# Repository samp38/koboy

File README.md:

# Kobo Mini to Flight Computer Kit

## Description
Turn your kobo mini into a complete flight instrument :-)
This project allows you to build an extension card for Kobo which runs XCSoar. The extension card includes a GPS and a pressure sensor. It acts as a sound variometer while it sends data (GPS NMEA data, Vz, temperature, absolute pressure) to XCSoar. In this repo you will find:
- Eagle files and guide to realize the electronic card
- Firmware source (and precompiled hex binaries) for the mcu
- STL parts for the Kobo Mini to receive electronic card (and a bigger battery for long flights)
- XCSoar software for Kobo

### How it works
The GPS chip is standalone. As long as it's powered, it runs and sends NMEA data through its TX output at a given (user definable) frequency. The microntroller manages the pressure sensing and computing: pressure is measured, numerically filtered and derivated at 50Hz to provide Vz. To work with the GPS chip, the microcontroller detects the beginning of the PA6H TX communication and waits the time needed to send variometer data between GPS data bursts. It can seem dubious but it works very well for years in my case. The variometer data sent by the microcontroller to XCSoar mimics a Digifly Leonardo. So you just have to select Digifly Leonardo in XCSoar to have the variometer data read and understood by XCSoar. All the steps of the XCSoar configuration is described in the __software__ part.

### Two versions for two interaction options
To control the sound vario volume and turn the extension card on/off (indeed, you might want to use your Kobo as a reader), there are two possibilities and thus two versions of the PCB:
- "button version": meaningful. Short press to loop in sound levels and long press to turn off.
- "tap-tap version": the button is replaced with a accelerometer which detects the tap. Single tap to loop in sound levels and double tap to turn on/off.

## Hardware

The extension card is based on a [PIC24F16KA101](http://ww1.microchip.com/downloads/en/DeviceDoc/39927c.pdf) microcontroller, a GPS patch antenna chip [(PA6H)](https://cdn-shop.adafruit.com/datasheets/GlobalTop-FGPMMOPA6H-Datasheet-V0A.pdf) and a high resolution pressure sensor [(MS5611)](https://infusionsystems.com/support/MS5611-01BA03.pdf).

The GPS (U5) symbol and footprint come from [Gekkio's KiCad libraries](https://github.com/Gekkio/gekkio-kicad-libs) by Joonas Javanainen, licensed under CC BY 4.0 (copy in `hardware/PCB/Vario Kobo/Button_version/kicad-koboy_button_side/libs/gekkio/`).

## Firmware

Compiled with Microchip XC16 compiler

## Software

XCSoar

## Open issues

### Schematic
- No VDD pin on the programming connector: the PIC must be powered separately while flashing.
- MCLR: the series resistor R2 (100Ω to 470Ω) from the datasheet's reference circuit is missing (C6 100nF sits directly on the MCLR net). It limits the current dumped by the capacitor if the pin breaks down under ESD/EOS (PIC24F16KA102 datasheet, §2.3).
- No local decoupling capacitor on the MAS6240 VIN.
- KOBO_RX is shared between the PIC and the GPS TX (through R5).
- Button version: the MAS6240 EN1/EN2 pins are wired to RA2/RA3, the reverse of `firmware/audio.c` (`EN1 = _RA3`, `EN2 = _RA2`). This dates back to the original Eagle design. As a result the low and medium volume levels are swapped (low gives 2x, medium gives 1x); high and off are unaffected. The taptap version matches the firmware. To be fixed in the firmware with per-version pin definitions.
- R7 (1Ω) in series with the piezo is nearly a jumper: the MAS6240 datasheet suggests an optional 1kΩ to 2kΩ output protection resistor.
- Taptap version: the PIC is programmed through the USB-A plug X1 with a custom pinout (D+ → MCLR, D− → PGC, 5V → PGD, which is also the GPS RX). Plugging the board into a real USB port would put 5V on PGD and the GPS RX.
- Taptap version: the PA6H GND pins 3, 12 and 19 are not connected (Eagle library), only pin 8 is. To be fixed with the Gekkio GPS footprint, as on the button version.

### PCB
- Button version, DRC: 2 silkscreen warnings, no errors: the BZ1 (buzzer) footprint outline from the Eagle import runs over its pads. The fab clips it.
- Taptap version, DRC: 12 errors, all pad-to-pad gaps of 0.195mm (rule 0.2mm) inside the Eagle MMA8452 footprint (0.305mm pads at 0.5mm pitch); to be fixed with a KiCad standard footprint. Silkscreen warnings from the Eagle PA6H and MMA8452 outlines and undersized texts.

### Firmware
- Auto-shutdown after inactivity is not implemented: `vario_shutdown_tick()` counts down but the `shutdown()` call is commented out (`firmware/vario.c`).

### Repository / documentation
- The hardware moved from Eagle to KiCad, with the same structure for both versions (`main` sheet plus a `Power supply` sub-sheet):
  - button version: `hardware/PCB/Vario Kobo/Button_version/kicad-koboy_button_side/main.kicad_pro`;
  - taptap version: `hardware/PCB/Vario Kobo/Taptap_version/kicad-koboy_taptap_side/main.kicad_pro` (migration in progress: references, silkscreen, GPS footprint and pin types still to do).

  The Eagle files are kept for history only; "Vario Kobo TOP" is to be removed.
- The README still says "Eagle files" in the description and needs updating for KiCad.

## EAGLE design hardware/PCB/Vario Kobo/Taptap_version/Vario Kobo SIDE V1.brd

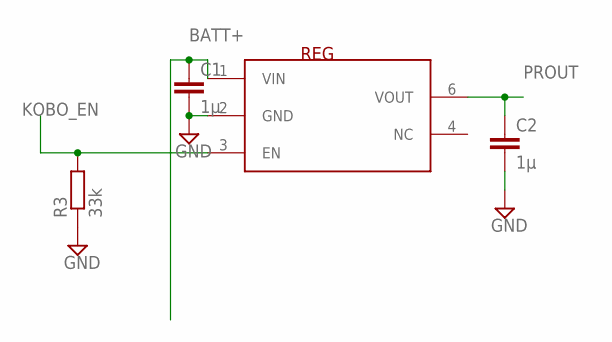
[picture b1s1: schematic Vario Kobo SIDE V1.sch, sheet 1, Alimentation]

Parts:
C1, C2: 1µ; C0603
R3: 33k; R0603
REG: ADP160/161/162/163; TSOT23-6_DDC

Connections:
BATT+: C1.1, REG.1 (VIN); also elsewhere on the board
GND: C1.2, C2.2, R3.1, REG.2 (GND); also elsewhere on the board
KOBO_EN: R3.2, REG.3 (EN); also elsewhere on the board
PROUT: C2.1, REG.6 (VOUT); also elsewhere on the board

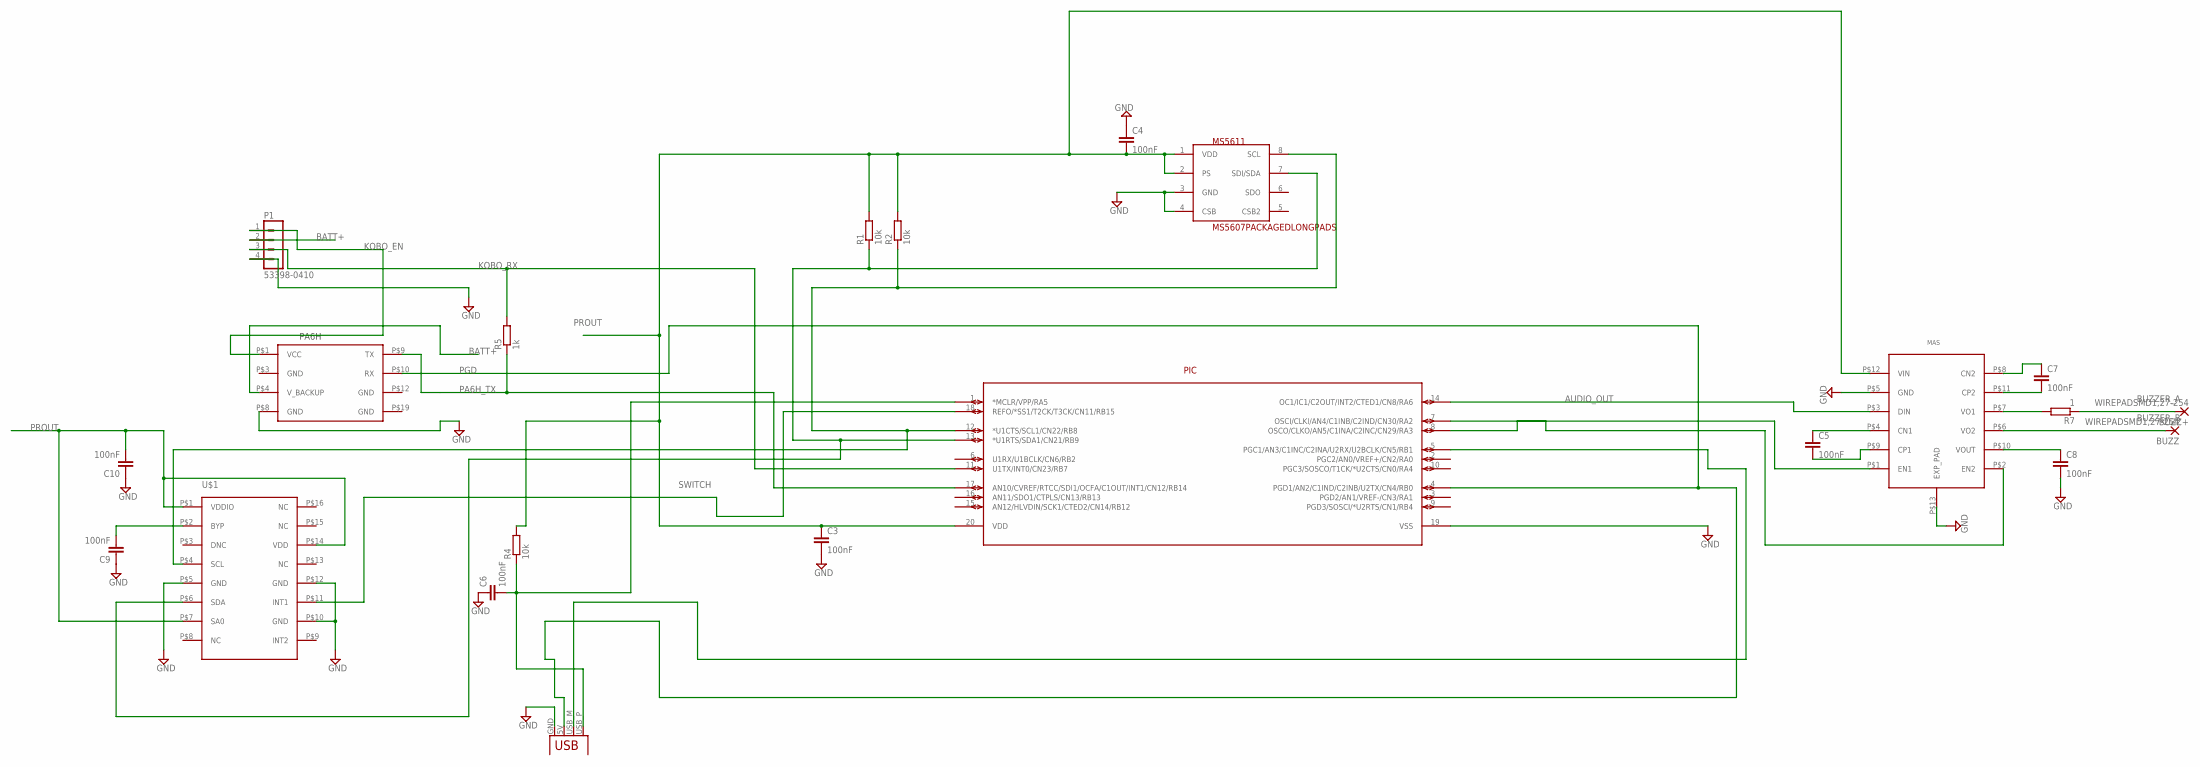
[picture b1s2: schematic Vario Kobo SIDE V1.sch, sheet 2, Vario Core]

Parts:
BUZZ: WIREPADSMD1,27-254; SMD1,27-2,54
BUZZ+: WIREPADSMD1,27-254; SMD1,27-2,54
C3, C4, C5, C6, C7, C8, C9, C10: 100nF; C0603
MAS: MAS6240; QFN12_3X3_LONGPADS
MS5611: MS5607PACKAGEDLONGPADS; MS5607-02BA03_LONGPADS
P1: 53398-0410
PA6H: PA6H; PA6H_PRINT
PIC: PIC24F16KA101-X_; SSOP20_MC
R1, R2, R4: 10k; R0603
R5: 1k; R0603
R7: 1; R0603
U$1: MMA8452LONGPADS; MMA845X_LONG_PADS
X1: USBPCB; USB-A-PCB

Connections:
AUDIO_OUT: MAS.P$3 (DIN), PIC.14 (OC1/IC1/C2OUT/INT2/CTED1/CN8/RA6)
BATT+: P1.2, PA6H.P$4 (V_BACKUP); also elsewhere on the board
BUZZER_A: BUZZ+.1, R7.1
BUZZER_B: BUZZ.1, MAS.P$6 (VO2)
GND: C3.2, C4.1, C6.1, C8.2, C9.1, C10.1, MAS.P$5 (GND), MAS.P$13 (EXP_PAD), MS5611.3 (GND), MS5611.4 (CSB), P1.4, PA6H.P$8 (GND), PIC.19 (VSS), U$1.P$5 (GND), U$1.P$10 (GND), U$1.P$12 (GND), X1.GND; also elsewhere on the board
KOBO_EN: P1.1, PA6H.P$1 (VCC); also elsewhere on the board
KOBO_RX: P1.3, PIC.11 (U1TX/INT0/CN23/RB7), R5.2
MCLR: C6.2, PIC.1 (*MCLR/VPP/RA5), R4.1, X1.USB_P (D+)
unnamed: C8.1, MAS.P$10 (VOUT)
unnamed: C5.1, MAS.P$4 (CN1)
unnamed: C5.2, MAS.P$9 (CP1)
unnamed: C7.2, MAS.P$11 (CP2)
unnamed: C7.1, MAS.P$8 (CN2)
unnamed: MAS.P$7 (VO1), R7.2
unnamed: MAS.P$1 (EN1), PIC.8 (OSCO/CLKO/AN5/C1INA/C2INC/CN29/RA3)
unnamed: C9.2, U$1.P$2 (BYP)
unnamed: MAS.P$2 (EN2), PIC.7 (OSCI/CLKI/AN4/C1INB/C2IND/CN30/RA2)
PA6H_TX: PA6H.P$9 (TX), PIC.17 (AN10/CVREF/RTCC/SDI1/OCFA/C1OUT/INT1/CN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), R5.1
PGC: PIC.5 (PGC1/AN3/C1INC/C2INA/U2RX/U2BCLK/CN5/RB1), X1.USB_M (D-)
PGD: PA6H.P$10 (RX), PIC.4 (PGD1/AN2/C1IND/C2INB/U2TX/CN4/RB0), X1.5V (VBUS)
PROUT: C3.1, C4.2, C10.2, MAS.P$12 (VIN), MS5611.1 (VDD), MS5611.2 (PS), PIC.20 (VDD), R1.2, R2.2, R4.2, U$1.P$1 (VDDIO), U$1.P$7 (SA0), U$1.P$14 (VDD); also elsewhere on the board
SCL: MS5611.8 (SCL), PIC.12 (*U1CTS/SCL1/CN22/RB8), R2.1, U$1.P$4 (SCL)
SDA: MS5611.7 (SDI/SDA), PIC.13 (*U1RTS/SDA1/CN21/RB9), R1.1, U$1.P$6 (SDA)
SWITCH: PIC.18 (REFO/*SS1/T2CK/T3CK/CN11/RB15), U$1.P$11 (INT1)

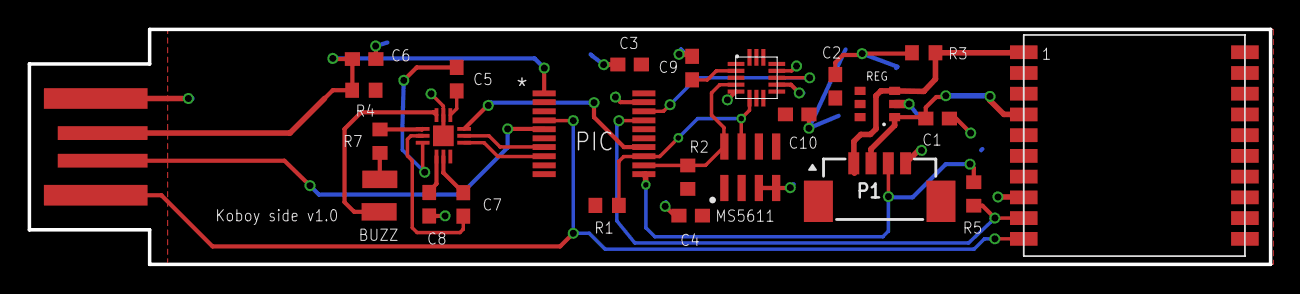
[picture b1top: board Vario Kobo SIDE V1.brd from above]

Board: 2 copper layers, 89.8 x 17.0 mm, 26 parts (0 on the bottom side), 24 nets.

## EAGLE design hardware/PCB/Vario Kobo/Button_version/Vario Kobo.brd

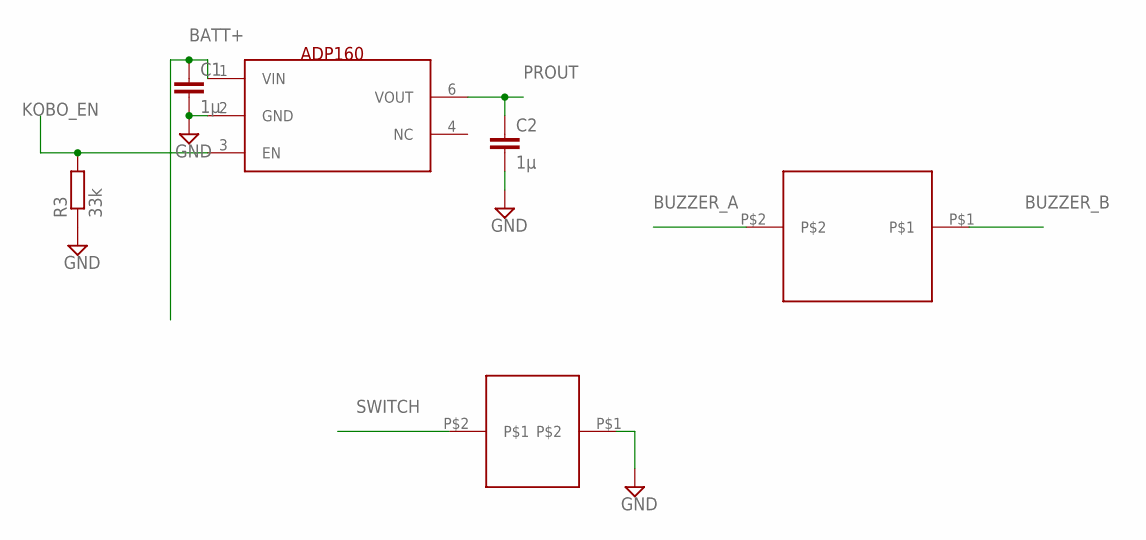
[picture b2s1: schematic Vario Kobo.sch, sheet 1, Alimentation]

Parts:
ADP160: ADP160/161/162/163; TSOT23-6_DDC
BUTTON: SMS_J_LEAD
BUZZER: PKLCS1212E2000-R1; PKLCS1212E2000-R1-SMD
C1, C2: 1µ; C0603
R3: 33k; R0603

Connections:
BATT+: ADP160.1 (VIN), C1.1; also elsewhere on the board
BUZZER_A: BUZZER.P$2; also elsewhere on the board
BUZZER_B: BUZZER.P$1; also elsewhere on the board
GND: ADP160.2 (GND), BUTTON.P$1, C1.2, C2.2, R3.1; also elsewhere on the board
KOBO_EN: ADP160.3 (EN), R3.2; also elsewhere on the board
PROUT: ADP160.6 (VOUT), C2.1; also elsewhere on the board
SWITCH: BUTTON.P$2; also elsewhere on the board

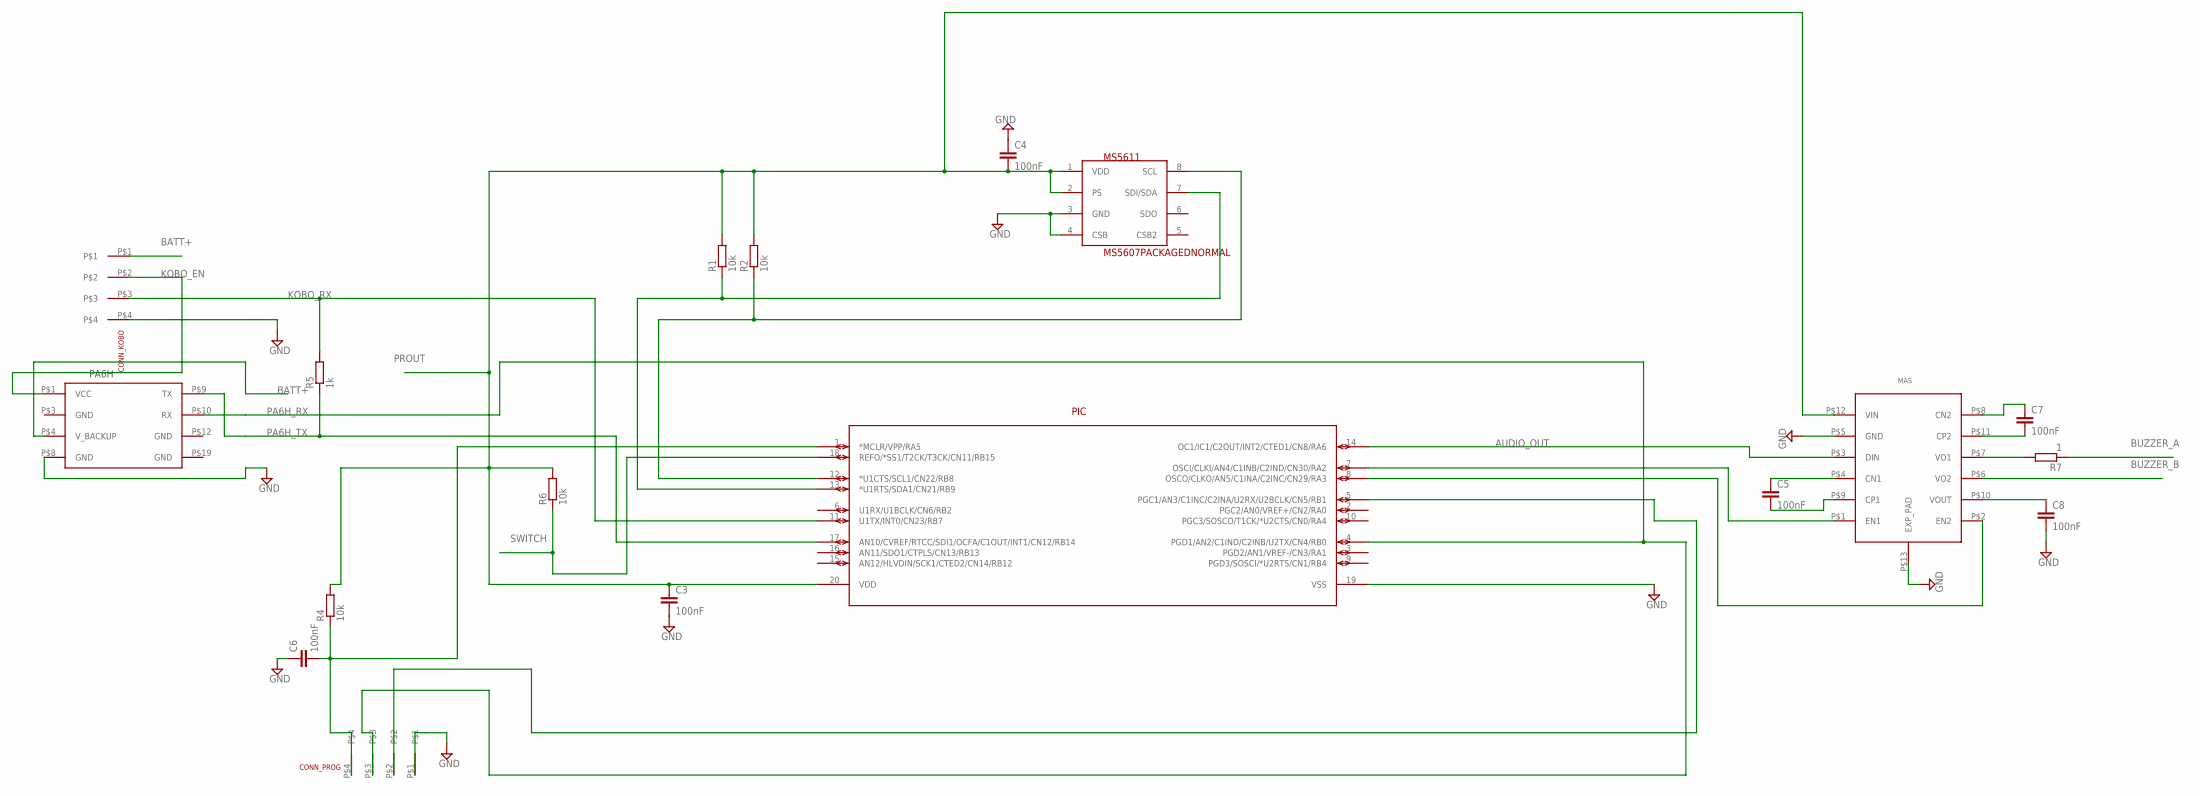
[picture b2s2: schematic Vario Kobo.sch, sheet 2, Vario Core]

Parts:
C3, C4, C5, C6, C7, C8: 100nF; C0603
CONN_KOBO: PICO-EZMATE4; PICO-EZMATE4-PCB
CONN_PROG: PICO-EZMATE4; PICO-EZMATE4-PCB
MAS: MAS6240; QFN12_3X3_LONGPADS
MS5611: MS5607PACKAGEDNORMAL; MS5607-02BA03
PA6H: PA6H; PA6H_PRINT
PIC: PIC24F16KA101-X_; SSOP20_MC
R1, R2, R4, R6: 10k; R0603
R5: 1k; R0603
R7: 1; R0603

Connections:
AUDIO_OUT: MAS.P$3 (DIN), PIC.14 (OC1/IC1/C2OUT/INT2/CTED1/CN8/RA6)
BATT+: CONN_KOBO.P$1, PA6H.P$4 (V_BACKUP); also elsewhere on the board
BUZZER_A: R7.1; also elsewhere on the board
BUZZER_B: MAS.P$6 (VO2); also elsewhere on the board
GND: C3.2, C4.1, C6.1, C8.2, CONN_KOBO.P$4, CONN_PROG.P$1, MAS.P$5 (GND), MAS.P$13 (EXP_PAD), MS5611.3 (GND), MS5611.4 (CSB), PA6H.P$8 (GND), PIC.19 (VSS); also elsewhere on the board
KOBO_EN: CONN_KOBO.P$2, PA6H.P$1 (VCC); also elsewhere on the board
KOBO_RX: CONN_KOBO.P$3, PIC.11 (U1TX/INT0/CN23/RB7), R5.2
MCLR: C6.2, CONN_PROG.P$4, PIC.1 (*MCLR/VPP/RA5), R4.1
unnamed: C8.1, MAS.P$10 (VOUT)
unnamed: C5.1, MAS.P$4 (CN1)
unnamed: C5.2, MAS.P$9 (CP1)
unnamed: C7.2, MAS.P$11 (CP2)
unnamed: C7.1, MAS.P$8 (CN2)
unnamed: MAS.P$7 (VO1), R7.2
unnamed: MAS.P$1 (EN1), PIC.7 (OSCI/CLKI/AN4/C1INB/C2IND/CN30/RA2)
unnamed: MAS.P$2 (EN2), PIC.8 (OSCO/CLKO/AN5/C1INA/C2INC/CN29/RA3)
PA6H_RX: CONN_PROG.P$3, PA6H.P$10 (RX), PIC.4 (PGD1/AN2/C1IND/C2INB/U2TX/CN4/RB0)
PA6H_TX: PA6H.P$9 (TX), PIC.17 (AN10/CVREF/RTCC/SDI1/OCFA/C1OUT/INT1/CN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), R5.1
PGC: CONN_PROG.P$2, PIC.5 (PGC1/AN3/C1INC/C2INA/U2RX/U2BCLK/CN5/RB1)
PROUT: C3.1, C4.2, MAS.P$12 (VIN), MS5611.1 (VDD), MS5611.2 (PS), PIC.20 (VDD), R1.2, R2.2, R4.2, R6.2; also elsewhere on the board
SCL: MS5611.8 (SCL), PIC.12 (*U1CTS/SCL1/CN22/RB8), R2.1
SDA: MS5611.7 (SDI/SDA), PIC.13 (*U1RTS/SDA1/CN21/RB9), R1.1
SWITCH: PIC.18 (REFO/*SS1/T2CK/T3CK/CN11/RB15), R6.1; also elsewhere on the board

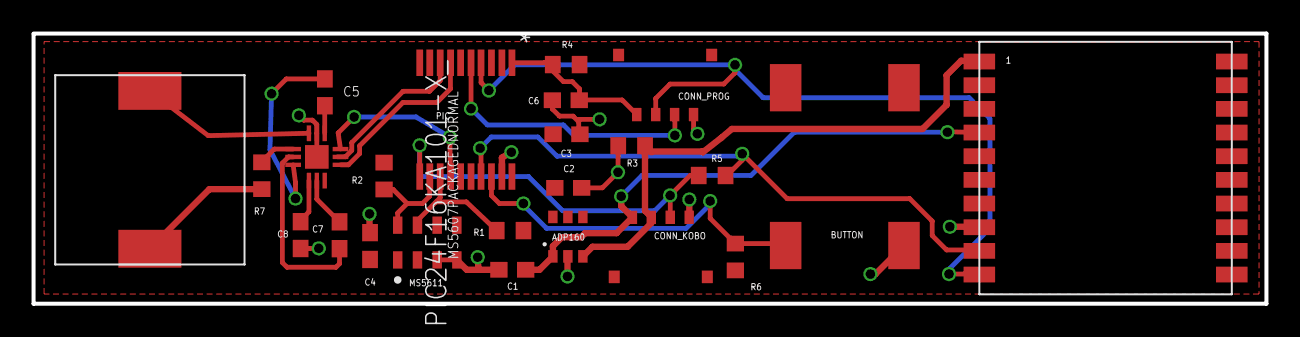
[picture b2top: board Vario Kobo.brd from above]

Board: 2 copper layers, 78.1 x 17.1 mm, 24 parts (0 on the bottom side), 23 nets.

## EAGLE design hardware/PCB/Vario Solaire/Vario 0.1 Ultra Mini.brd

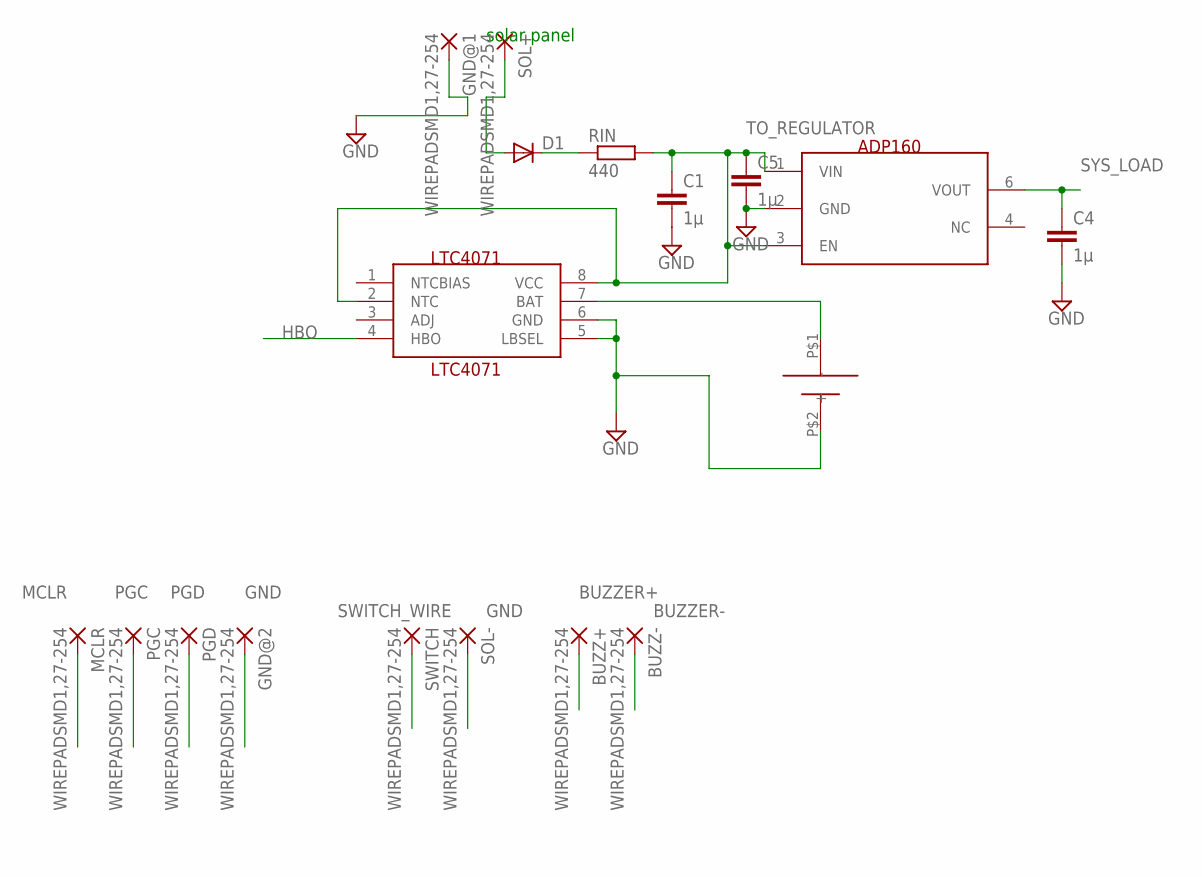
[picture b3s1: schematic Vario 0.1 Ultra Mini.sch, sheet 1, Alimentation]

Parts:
ADP160: ADP160/161/162/163; TSOT23-6_DDC
BATT+: VARIO_LIPO
BUZZ+: WIREPADSMD1,27-254; SMD1,27-2,54
BUZZ-: WIREPADSMD1,27-254; SMD1,27-2,54
C1, C4, C5: 1µ; C0603
D1: DIODE-SOD323-R; SOD323-R
GND@1, GND@2: WIREPADSMD1,27-254; SMD1,27-2,54
LTC4071: LTC4071; MSOP8
MCLR: WIREPADSMD1,27-254; SMD1,27-2,54
PGC: WIREPADSMD1,27-254; SMD1,27-2,54
PGD: WIREPADSMD1,27-254; SMD1,27-2,54
RIN: 440; R0603
SOL+: WIREPADSMD1,27-254; SMD1,27-2,54
SOL-: WIREPADSMD1,27-254; SMD1,27-2,54
SWITCH: WIREPADSMD1,27-254; SMD1,27-2,54

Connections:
BATT: BATT+.P$1 (+), LTC4071.7 (BAT)
BUZZER+: BUZZ+.1; also elsewhere on the board
BUZZER-: BUZZ-.1; also elsewhere on the board
GND: ADP160.2 (GND), BATT+.P$2 (-), C1.2, C4.2, C5.2, GND@1.1, GND@2.1, LTC4071.5 (LBSEL), LTC4071.6 (GND), SOL-.1; also elsewhere on the board
HBO: LTC4071.4 (HBO)
MCLR: MCLR.1; also elsewhere on the board
unnamed: D1.C, RIN.1
PGC: PGC.1; also elsewhere on the board
PGD: PGD.1; also elsewhere on the board
SOL+: D1.A, SOL+.1
SWITCH_WIRE: SWITCH.1; also elsewhere on the board
SYS_LOAD: ADP160.6 (VOUT), C4.1; also elsewhere on the board
TO_REGULATOR: ADP160.1 (VIN), ADP160.3 (EN), C1.1, C5.1, LTC4071.2 (NTC), LTC4071.8 (VCC), RIN.2

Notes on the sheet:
solar panel

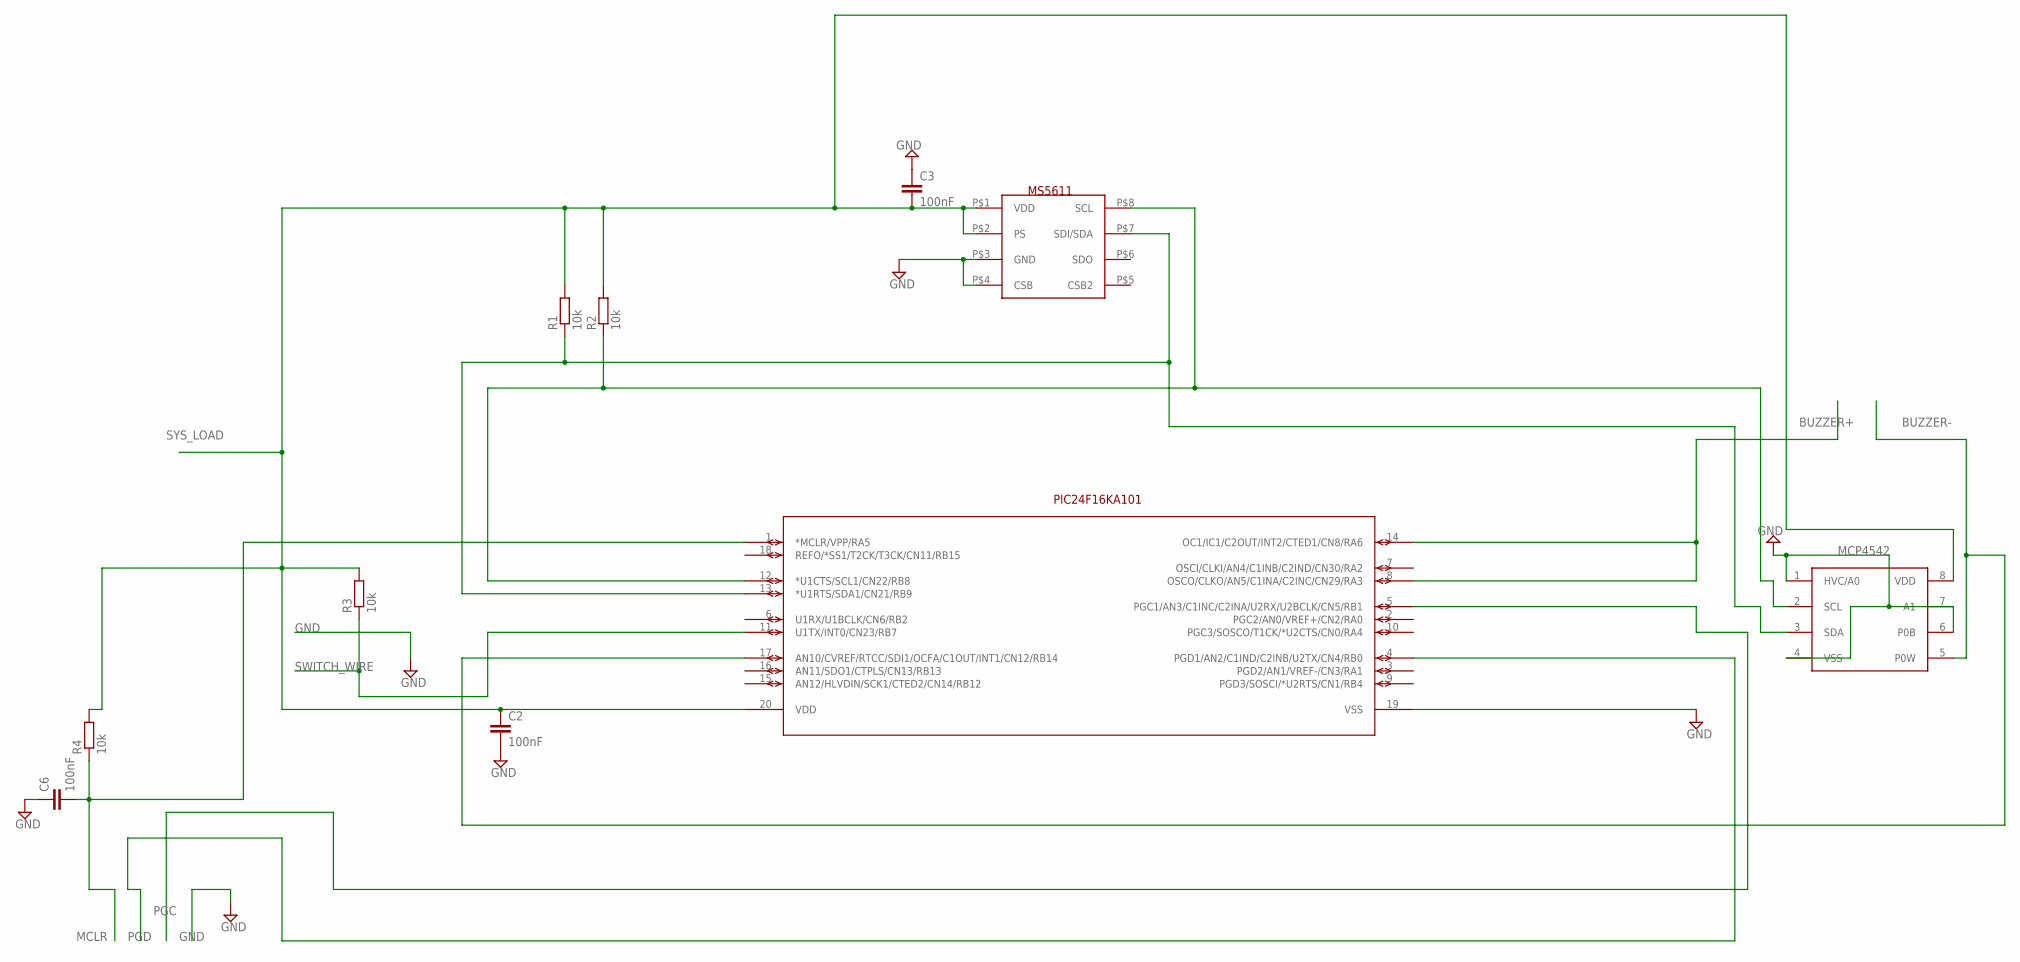
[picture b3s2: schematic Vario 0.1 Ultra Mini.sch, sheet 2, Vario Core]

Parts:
C2, C3, C6: 100nF; C0603
MCP4542: MCP4542; MSOP8
MS5611: MS5607PACKAGED; MS5607-02BA03
PIC24F16KA101: PIC24F16KA101-X_; SSOP20_MC
R1, R2, R3, R4: 10k; R0603

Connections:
BUZZER+: PIC24F16KA101.8 (OSCO/CLKO/AN5/C1INA/C2INC/CN29/RA3), PIC24F16KA101.14 (OC1/IC1/C2OUT/INT2/CTED1/CN8/RA6); also elsewhere on the board
BUZZER-: MCP4542.5 (P0W), PIC24F16KA101.17 (AN10/CVREF/RTCC/SDI1/OCFA/C1OUT/INT1/CN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); also elsewhere on the board
GND: C2.2, C3.1, C6.1, MCP4542.1 (HVC/A0), MCP4542.4 (VSS), MCP4542.6 (P0B), MCP4542.7 (A1), MS5611.P$3 (GND), MS5611.P$4 (CSB), PIC24F16KA101.19 (VSS); also elsewhere on the board
MCLR: C6.2, PIC24F16KA101.1 (*MCLR/VPP/RA5), R4.1; also elsewhere on the board
PGC: PIC24F16KA101.5 (PGC1/AN3/C1INC/C2INA/U2RX/U2BCLK/CN5/RB1); also elsewhere on the board
PGD: PIC24F16KA101.4 (PGD1/AN2/C1IND/C2INB/U2TX/CN4/RB0); also elsewhere on the board
SCL: MCP4542.2 (SCL), MS5611.P$8 (SCL), PIC24F16KA101.12 (*U1CTS/SCL1/CN22/RB8), R2.1
SDA: MCP4542.3 (SDA), MS5611.P$7 (SDI/SDA), PIC24F16KA101.13 (*U1RTS/SDA1/CN21/RB9), R1.1
SWITCH_WIRE: PIC24F16KA101.11 (U1TX/INT0/CN23/RB7), R3.1; also elsewhere on the board
SYS_LOAD: C2.1, C3.2, MCP4542.8 (VDD), MS5611.P$1 (VDD), MS5611.P$2 (PS), PIC24F16KA101.20 (VDD), R1.2, R2.2, R3.2, R4.2; also elsewhere on the board

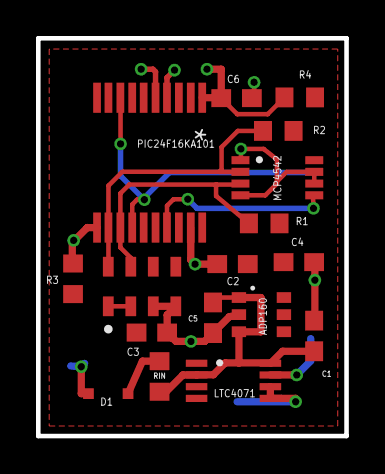
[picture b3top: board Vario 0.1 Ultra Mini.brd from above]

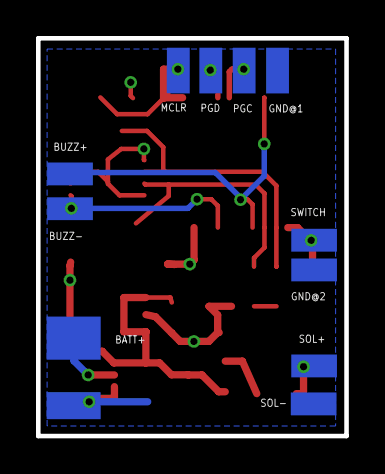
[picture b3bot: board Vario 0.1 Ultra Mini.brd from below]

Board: 2 copper layers, 17.1 x 22.1 mm, 28 parts (11 on the bottom side), 14 nets.

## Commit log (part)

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2016-09-08 First one
    Add Readme
2016-09-08 Add details to README
2016-09-08 Import files
2016-09-08 Correct oscillator frequency comment
2016-09-08 Complete README
2016-09-08 Makefiles and clean some old backups
2016-09-08 clean files
2016-09-09 Clean 3D Files and docs
    Ignoring makefiles
2017-01-23 readme
2017-01-23 réadmet
2018-06-05 cleaning up
2018-06-05 CLEAN

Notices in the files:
parts and their libraries:
con-molex-picoblade: Copyright (C) 2010, Bob Starr
